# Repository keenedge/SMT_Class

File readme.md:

kikit panelize --framing "frame; width: 3.5mm; space: 2mm" --tabs "annotation; width: 3mm" --cuts "mousebites; drill: 0.5mm; spacing: 0.8mm; offset: -0.25mm" --post "millradius: 1mm" smt_tree.kicad_pcb smt_tree_with_frame.kicad_pcb

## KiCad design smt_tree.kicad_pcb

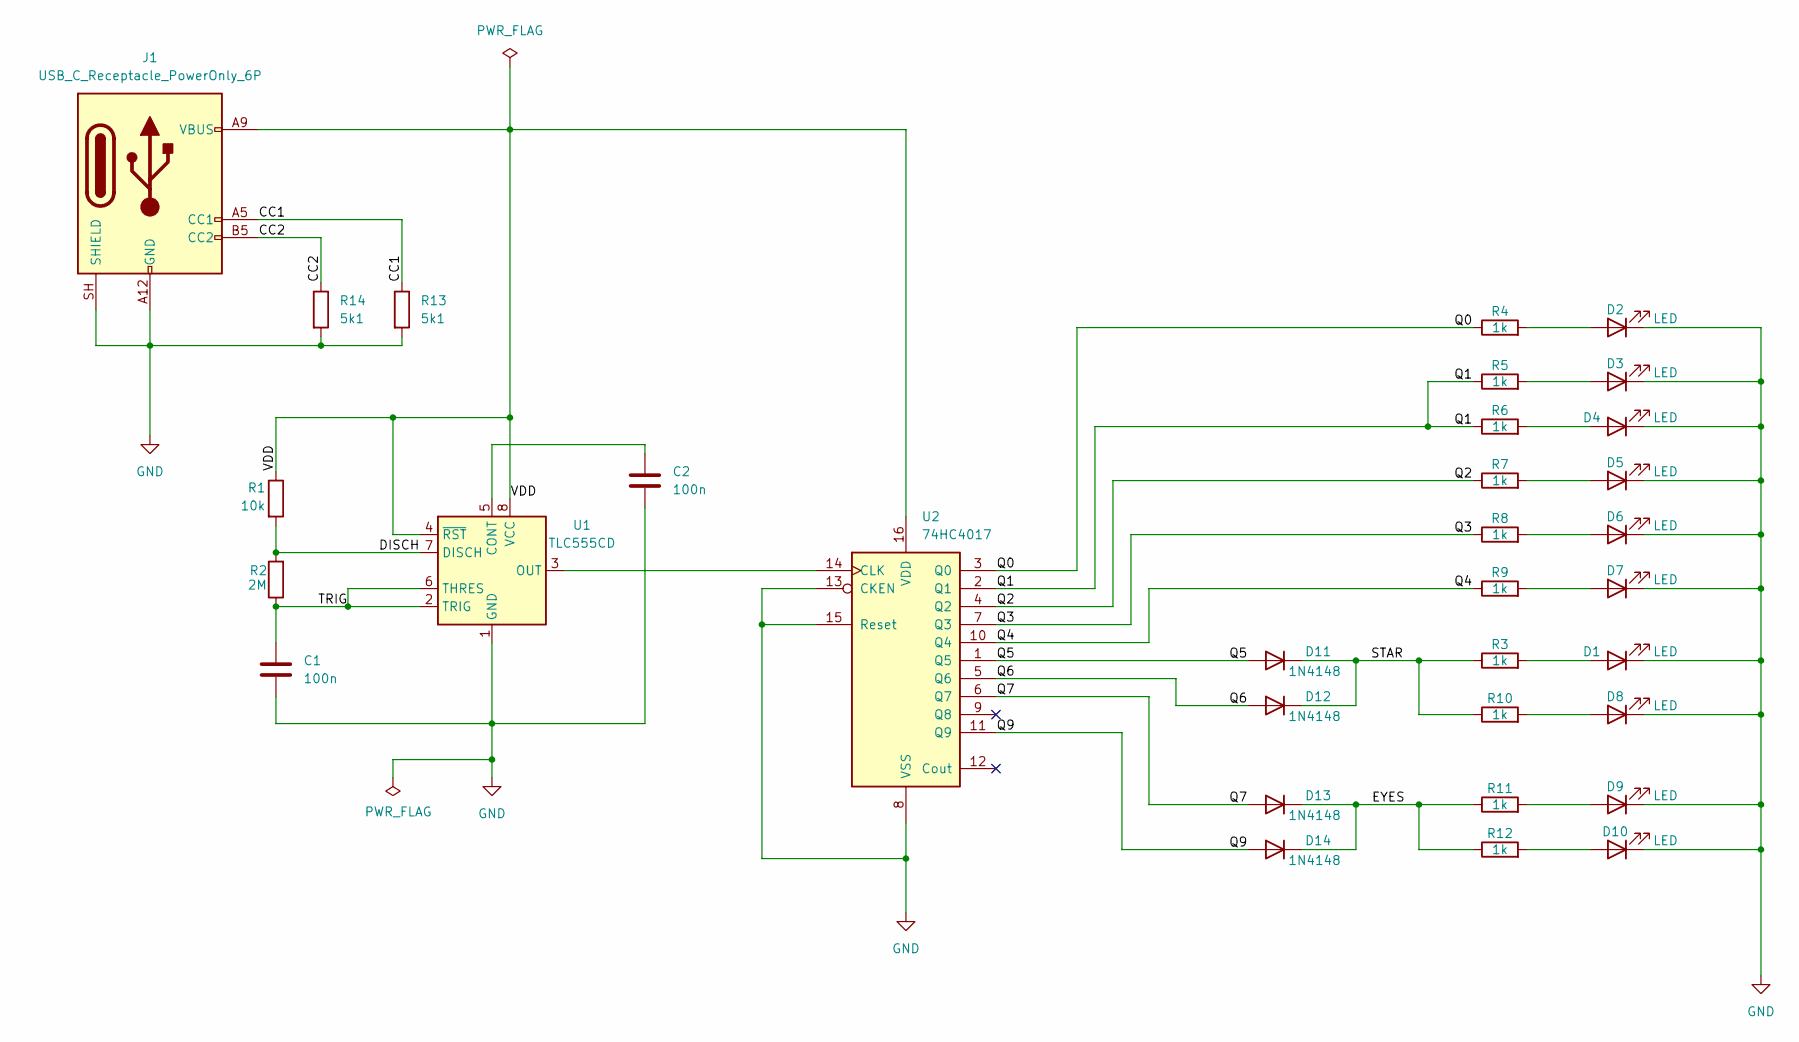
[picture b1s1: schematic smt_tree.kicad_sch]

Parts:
C1, C2: 100n; C_0805_2012Metric
D1, D2, D3, D4, D5, D6, D7, D8, D9, D10: LED; LED_0805_2012Metric
D11, D12, D13, D14: 1N4148; D_0805_2012Metric
J1: USB_C_Receptacle_PowerOnly_6P; USB_C_Receptacle_GCT_USB4135-GF-A_6P_TopMnt_Horizontal
R1: 10k; R_0805_2012Metric
R2: 2M; R_0805_2012Metric
R3, R4, R5, R6, R7, R8, R9, R10, R11, R12: 1k; R_0805_2012Metric
R13, R14: 5k1; R_0805_2012Metric
U1: TLC555CD; SOIC-8_3.9x4.9mm_P1.27mm
U2: 74HC4017; SOIC-16_3.9x9.9mm_P1.27mm

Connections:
/CC1: J1.A5 (CC1), R13.1
/CC2: J1.B5 (CC2), R14.1
/DISCH: R1.2, R2.2, U1.7 (DISCH)
/EYES: D13.1 (K), D14.1 (K), R11.1, R12.1
/Q0: R4.1, U2.3 (Q0)
/Q1: R5.1, R6.1, U2.2 (Q1)
/Q2: R7.1, U2.4 (Q2)
/Q3: R8.1, U2.7 (Q3)
/Q4: R9.1, U2.10 (Q4)
/Q5: D11.2 (A), U2.1 (Q5)
/Q6: D12.2 (A), U2.5 (Q6)
/Q7: D13.2 (A), U2.6 (Q7)
/Q9: D14.2 (A), U2.11 (Q9)
/STAR: D11.1 (K), D12.1 (K), R3.1, R10.1
/TRIG: C1.1, R2.1, U1.2 (TRIG), U1.6 (THRES)
/VDD: J1.A9 (VBUS), J1.B9 (VBUS), R1.1, U1.4 (~RST), U1.8 (VCC), U2.16 (VDD)
GND: C1.2, C2.2, D1.1 (K), D2.1 (K), D3.1 (K), D4.1 (K), D5.1 (K), D6.1 (K), D7.1 (K), D8.1 (K), D9.1 (K), D10.1 (K), J1.A12 (GND), J1.B12 (GND), J1.SH (SHIELD), R13.2, R14.2, U1.1 (GND), U2.8 (VSS), U2.13 (CKEN), U2.15 (Reset)
unnamed: D1.2 (A), R3.2
unnamed: D2.2 (A), R4.2
unnamed: D3.2 (A), R5.2
unnamed: D4.2 (A), R6.2
unnamed: D5.2 (A), R7.2
unnamed: D6.2 (A), R8.2
unnamed: D7.2 (A), R9.2
unnamed: D8.2 (A), R10.2
unnamed: D9.2 (A), R11.2
unnamed: D10.2 (A), R12.2
unnamed: C2.1, U1.5 (CONT)
unnamed: U1.3 (OUT), U2.14 (CLK)

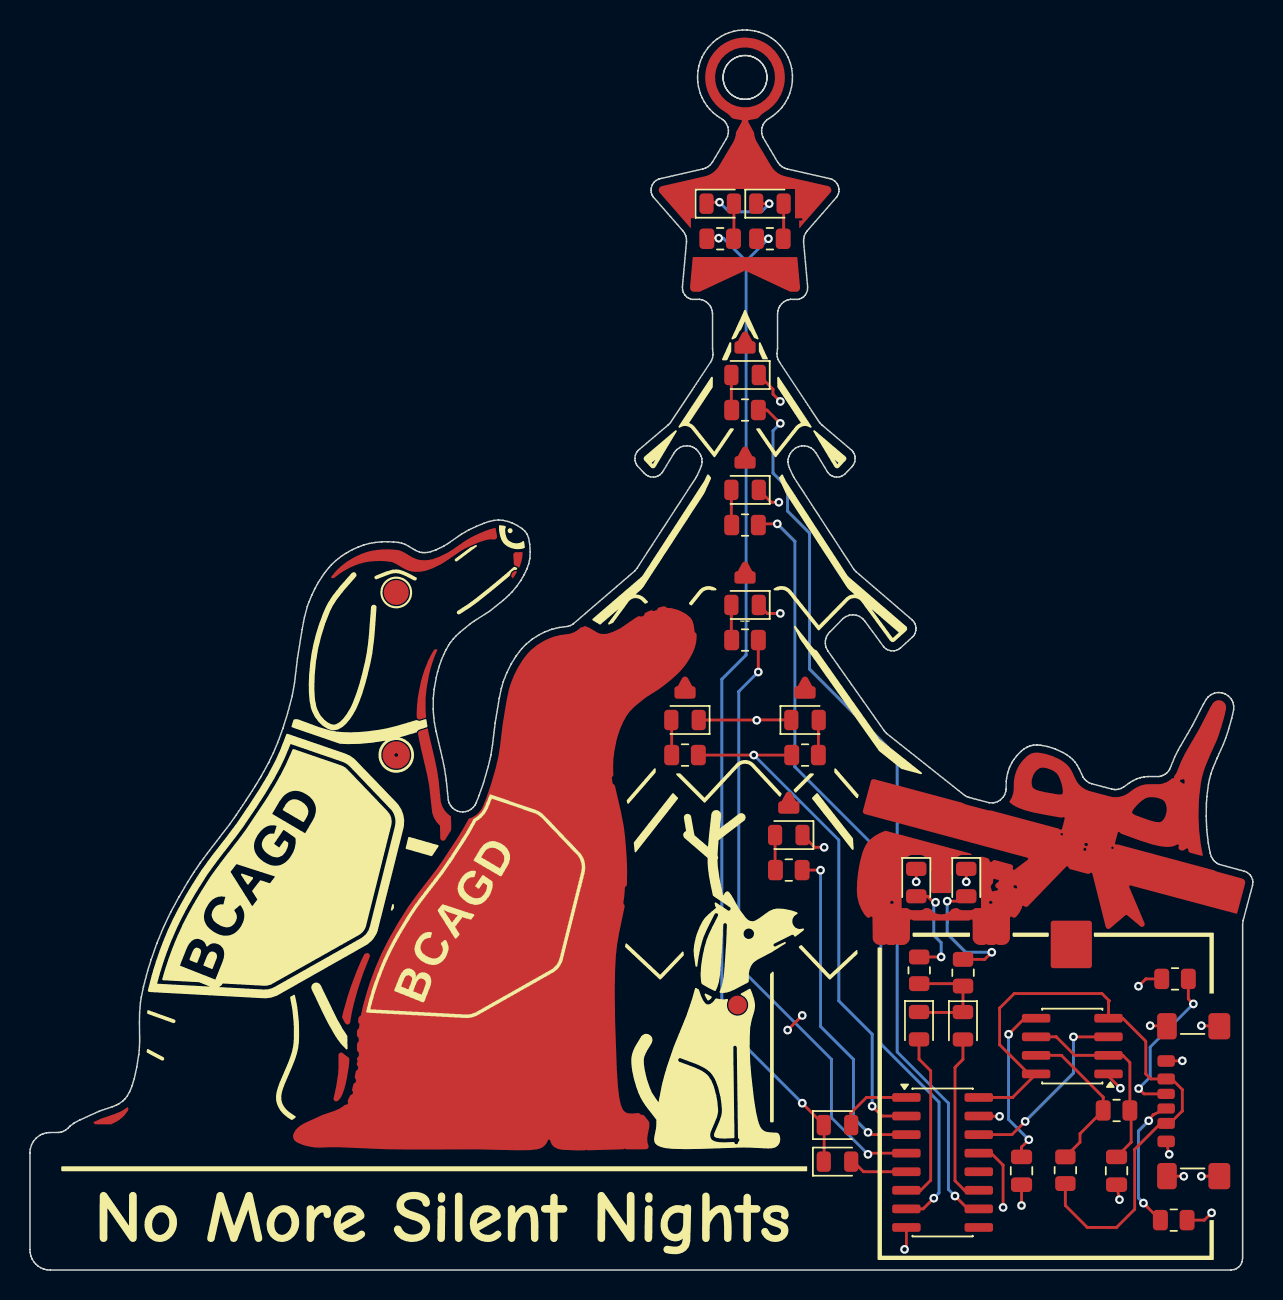
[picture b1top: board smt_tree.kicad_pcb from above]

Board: 2 copper layers, 83.7 x 84.8 mm, 33 parts (0 on the bottom side), 29 nets.
